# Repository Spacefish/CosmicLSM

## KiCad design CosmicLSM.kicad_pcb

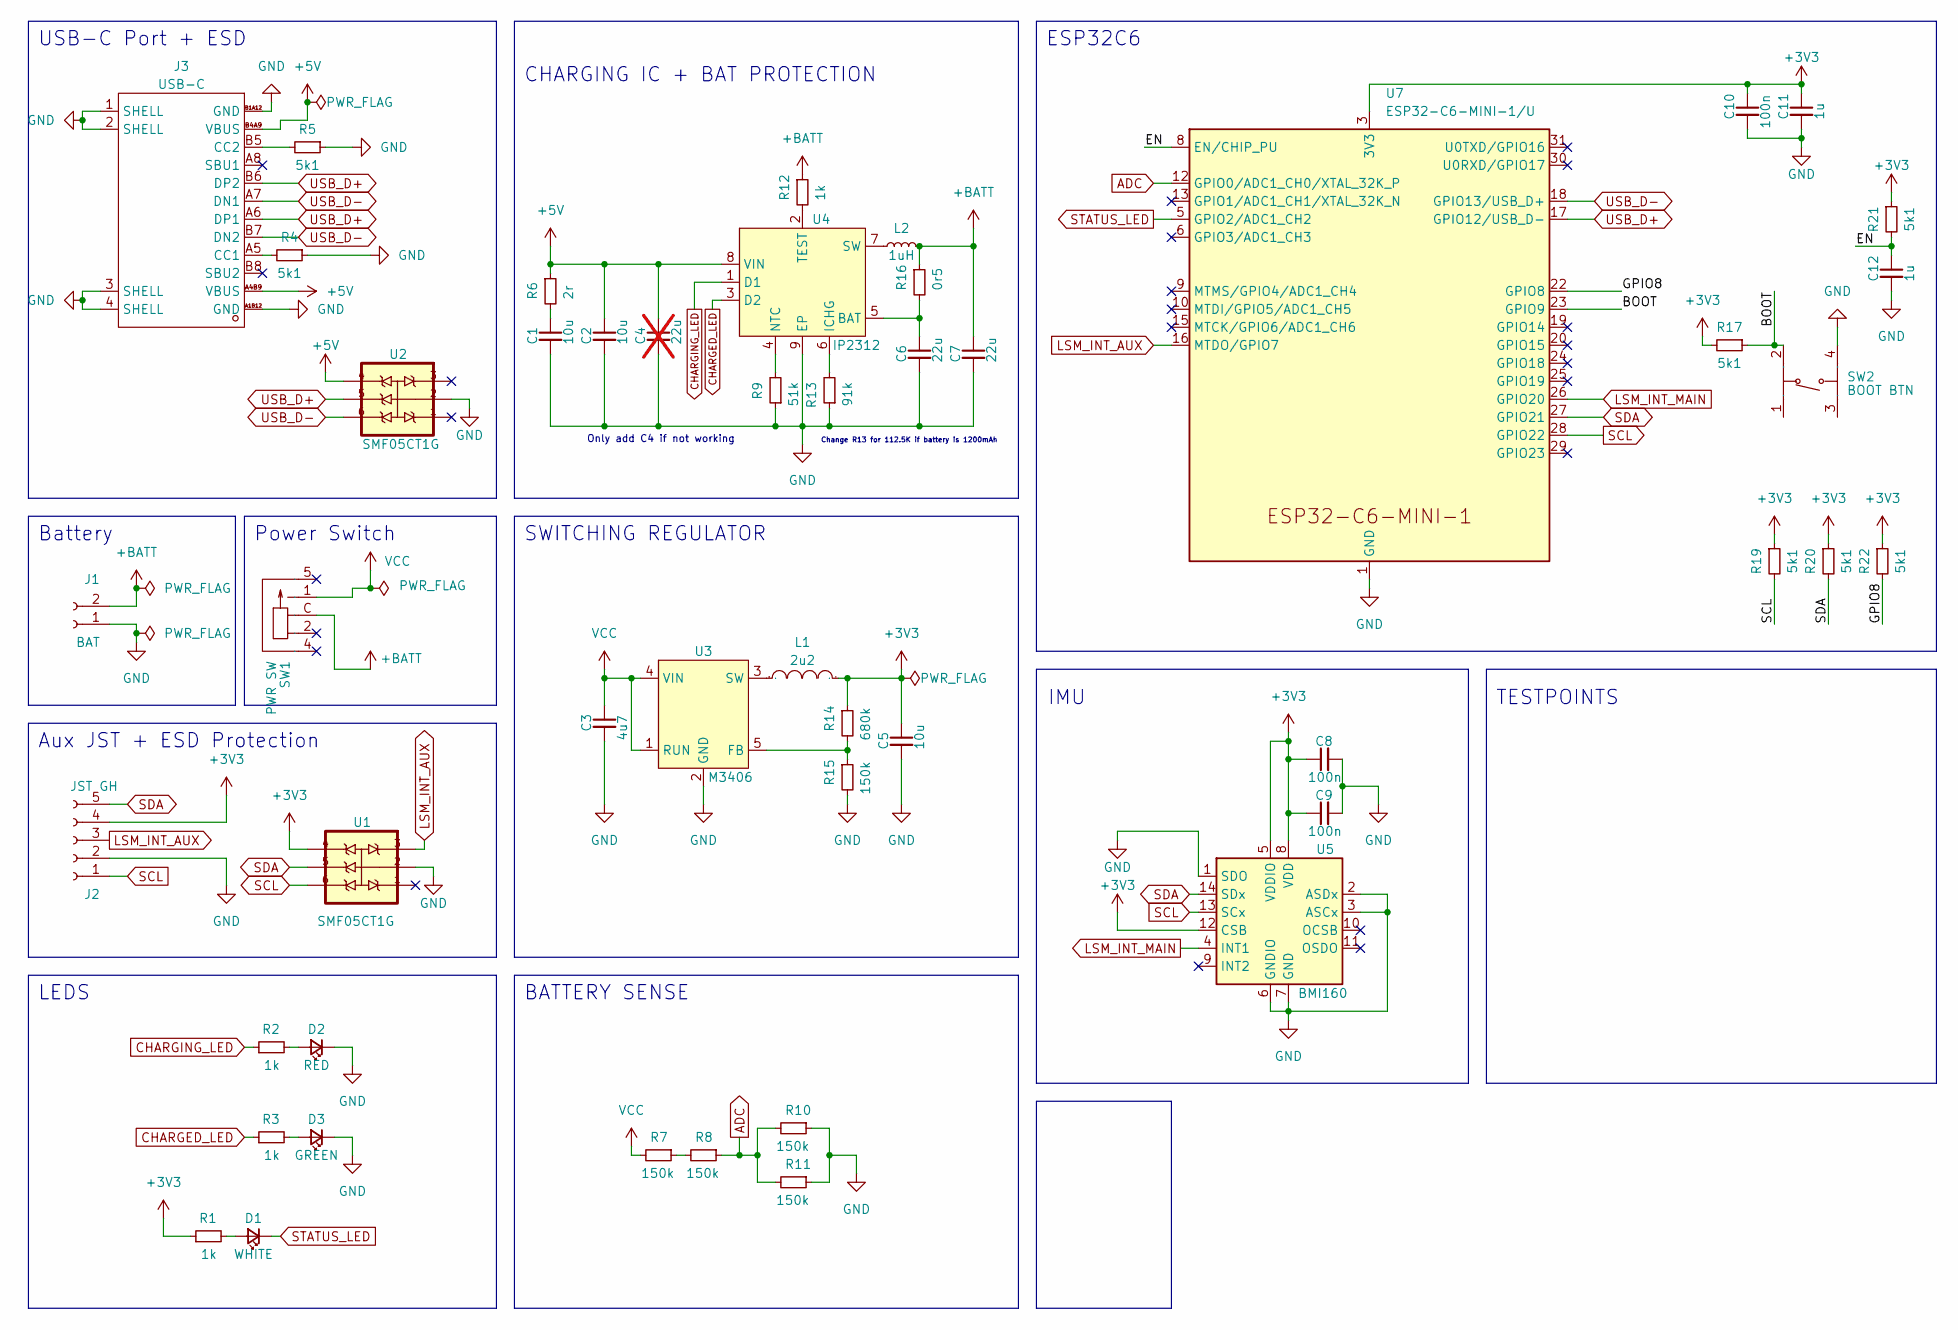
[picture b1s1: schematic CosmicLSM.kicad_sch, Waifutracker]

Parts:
C1, C2, C5: 10u; C_0603_1608Metric_Pad1.08x0.95mm_HandSolder
C3: 4u7; C_0603_1608Metric_Pad1.08x0.95mm_HandSolder
C4: 22u; C_0603_1608Metric_Pad1.08x0.95mm_HandSolder; not fitted
C6, C7: 22u; C_0603_1608Metric_Pad1.08x0.95mm_HandSolder
C8, C9, C10: 100n; C_0603_1608Metric_Pad1.08x0.95mm_HandSolder
C11, C12: 1u; C_0603_1608Metric_Pad1.08x0.95mm_HandSolder
D1: WHITE; LED_0603_1608Metric_Pad1.05x0.95mm_HandSolder; LCSC C2290
D2: RED; LED_0603_1608Metric_Pad1.05x0.95mm_HandSolder; LCSC C2286
D3: GREEN; LED_0603_1608Metric_Pad1.05x0.95mm_HandSolder; LCSC C72038
J1: BAT; JST_PH_S2B-PH-SM4-TB_1x02-1MP_P2.00mm_Horizontal; LCSC C295747
J2: JST GH; JST_GH_SM05B-GHS-TB_1x05-1MP_P1.25mm_Horizontal
J3: USB-C; USB-C-SMD_G-SWITCH_GT-USB-7010ASV; LCSC C2988369
L1: 2u2; IND-SMD_L2.0-W1.6_GCDA201610P-R24MC; LCSC C439304
L2: 1uH; L_1008_2520Metric_Pad1.43x2.20mm_HandSolder; LCSC C2043089
R1, R2, R3, R12: 1k; R_0603_1608Metric_Pad0.98x0.95mm_HandSolder
R4, R5, R17, R19, R20, R21, R22: 5k1; R_0603_1608Metric_Pad0.98x0.95mm_HandSolder
R6: 2r; R_0603_1608Metric_Pad0.98x0.95mm_HandSolder
R7, R8, R10, R11, R15: 150k; R_0603_1608Metric_Pad0.98x0.95mm_HandSolder
R9: 51k; R_0603_1608Metric_Pad0.98x0.95mm_HandSolder
R13: 91k; R_0603_1608Metric_Pad0.98x0.95mm_HandSolder
R14: 680k; R_0603_1608Metric_Pad0.98x0.95mm_HandSolder
R16: 0r5; R_0603_1608Metric_Pad0.98x0.95mm_HandSolder
SW1: PWR SW; SW-SMD_MK-11C04-G013; LCSC C778185
SW2: BOOT BTN; SW-SMD_4P-L5.1-W5.1-P3.70-LS6.5-TL-2; LCSC C318884
U1, U2: SMF05CT1G; SOT-363_SC-70-6
U3: M3406; SOT-23-5; LCSC C83224
U4: IP2312; HSOP-8-1EP_3.9x4.9mm_P1.27mm_EP2.41x3.1mm
U5: BMI160; Bosch_LGA-14_3x2.5mm_P0.5mm
U7: ESP32-C6-MINI-1/U; ESP32-C6-MINI-1

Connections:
+3V3: C5.1, C8.1, C9.1, C10.1, C11.1, J2.4, L1.2, R1.1, R14.1, R17.2, R19.1, R20.1, R21.1, R22.1, U1.4, U5.5 (VDDIO), U5.8 (VDD), U5.12 (CSB), U7.3 (3V3)
+5V: C2.1, C4.1, J3.A4B9 (VBUS), J3.B4A9 (VBUS), R6.1, U2.4, U4.8 (VIN)
+BATT: C7.1, J1.2 (Pin_1), L2.2, R12.1, R16.1, SW1.C
/BOOT: R17.1, SW2.2 (B), U7.23 (GPIO9)
/EN: C12.1, R21.2, U7.8 (EN/CHIP_PU)
/GPIO8: R22.2, U7.22 (GPIO8)
ADC: R8.1, R10.2, R11.2, U7.12 (GPIO0/ADC1_CH0/XTAL_32K_P)
CHARGED_LED: R3.1, U4.3 (D2)
CHARGING_LED: R2.1, U4.1 (D1)
GND: C1.2, C2.2, C3.2, C4.2, C5.2, C6.2, C7.2, C8.2, C9.2, C10.2, C11.2, C12.2, D2.1 (K), D3.1 (K), J1.1 (Pin_2), J2.2, J3.1 (SHELL), J3.2 (SHELL), J3.3 (SHELL), J3.4 (SHELL), J3.A1B12 (GND), J3.B1A12 (GND), R4.1, R5.1, R9.1, R10.1, R11.1, R13.1, R15.2, SW2.4 (D), U1.2, U2.2, U3.2 (GND), U4.9 (EP), U5.1 (SDO), U5.2 (ASDx), U5.3 (ASCx), U5.6 (GNDIO), U5.7 (GND), U7.1 (GND), U7.2 (GND), U7.11 (GND), U7.14 (GND), U7.36 (GND), U7.37 (GND), U7.38 (GND), U7.39 (GND), U7.40 (GND), U7.41 (GND), U7.42 (GND), U7.43 (GND), U7.44 (GND), U7.45 (GND), U7.46 (GND), U7.47 (GND), U7.48 (GND), U7.49 (GND), U7.50 (GND), U7.51 (GND), U7.52 (GND), U7.53 (GND)
LSM_INT_AUX: J2.3, U1.3, U7.16 (MTDO/GPIO7)
LSM_INT_MAIN: U5.4 (INT1), U7.26 (GPIO20)
unnamed: C1.1, R6.2
unnamed: D1.2 (A), R1.2
unnamed: D2.2 (A), R2.2
unnamed: D3.2 (A), R3.2
unnamed: J3.A5 (CC1), R4.2
unnamed: J3.B5 (CC2), R5.2
unnamed: R7.1, R8.2
unnamed: R14.2, R15.1, U3.5 (FB)
unnamed: L1.1, U3.3 (SW)
unnamed: C6.1, R16.2, U4.5 (BAT)
unnamed: R13.2, U4.6 (ICHG)
unnamed: R9.2, U4.4 (NTC)
unnamed: L2.1, U4.7 (SW)
unnamed: R12.2, U4.2 (TEST)
SCL: J2.1, R19.2, U1.6, U5.13 (SCx), U7.28 (GPIO22)
SDA: J2.5, R20.2, U1.5, U5.14 (SDx), U7.27 (GPIO21)
STATUS_LED: D1.1 (K), U7.5 (GPIO2/ADC1_CH2)
USB_D+: J3.A6 (DP1), J3.B6 (DP2), U2.5, U7.17 (GPIO12/USB_D-)
USB_D-: J3.A7 (DN1), J3.B7 (DN2), U2.6, U7.18 (GPIO13/USB_D+)
VCC: C3.1, R7.2, SW1.1, U3.1 (RUN), U3.4 (VIN)

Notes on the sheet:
Battery
Only add C4 if not working
SWITCHING REGULATOR
ESP32C6
TESTPOINTS
USB-C Port + ESD
IMU
Aux JST + ESD Protection
BATTERY SENSE
Change R13 for 112.5K if battery is 1200mAh
Power Switch
CHARGING IC + BAT PROTECTION
LEDS

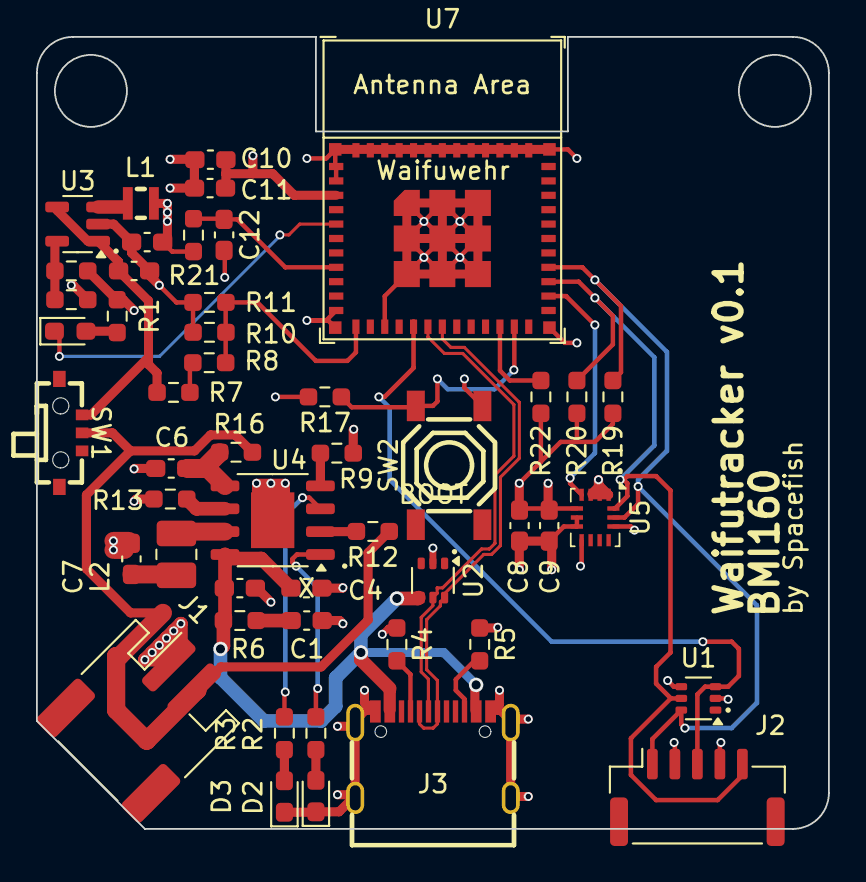
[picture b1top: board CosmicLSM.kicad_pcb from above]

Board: 4 copper layers, 44.0 x 44.0 mm, 49 parts (0 on the bottom side), 32 nets.

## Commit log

2024-05-07 use ESP32-C6 in schematic
2024-05-08 new data
2024-05-08 update to pcb
2024-05-08 remove backup files
2024-05-08 ignore temporary files
2024-05-09 inductors
2024-05-09 ordered
2024-05-09 add notes

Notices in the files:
CosmicLSM.kicad_sch:
Licensed under CERN-OHL-P 2
